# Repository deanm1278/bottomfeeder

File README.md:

# bottomfeeder

demo video of the synthesizer with a control panel added on top is [here](https://youtu.be/Ub5NRgZzTfE).
Note the synthesizer is mounted to the back of the panel in the video.

Features include:
- 3x 16 bit digital Wavetable Oscillators (sample rates up to 200k samples/sec)
  - Fine and coarse tuning controls for each oscillator
  - user loadable waveforms
  - 1 square wave sub oscillator for each oscillator
- Full analog 4 pole resonant low pass filter
- ADSR envelope generator mappable to filter cutoff and VCA
- Monophonic and 3 voice Paraphonic modes
- Glide rate control
- 2x LFO (also any user loadable waveform)
  - Mappable to many parameters including rate or depth of the other LFO
- Headphone output
- External input to filter
- All parameters controllable via Standard MIDI
- Header connections for modification
- Loading and saving presets
- Low cost and small form factor

## Structure
An ARM Cortex M0+ microcontroller acts as a host processor for an [FPGA-Based synthesizer](https://github.com/deanm1278/Chisel-wavetable).
The FPGA outputs the oscillators as well as PWM control voltages for the analog filter and analog VCA parameters.
[Click here](https://github.com/deanm1278/bottomfeeder/blob/master/schematics/synth_revD.pdf) to view PDF schematics.

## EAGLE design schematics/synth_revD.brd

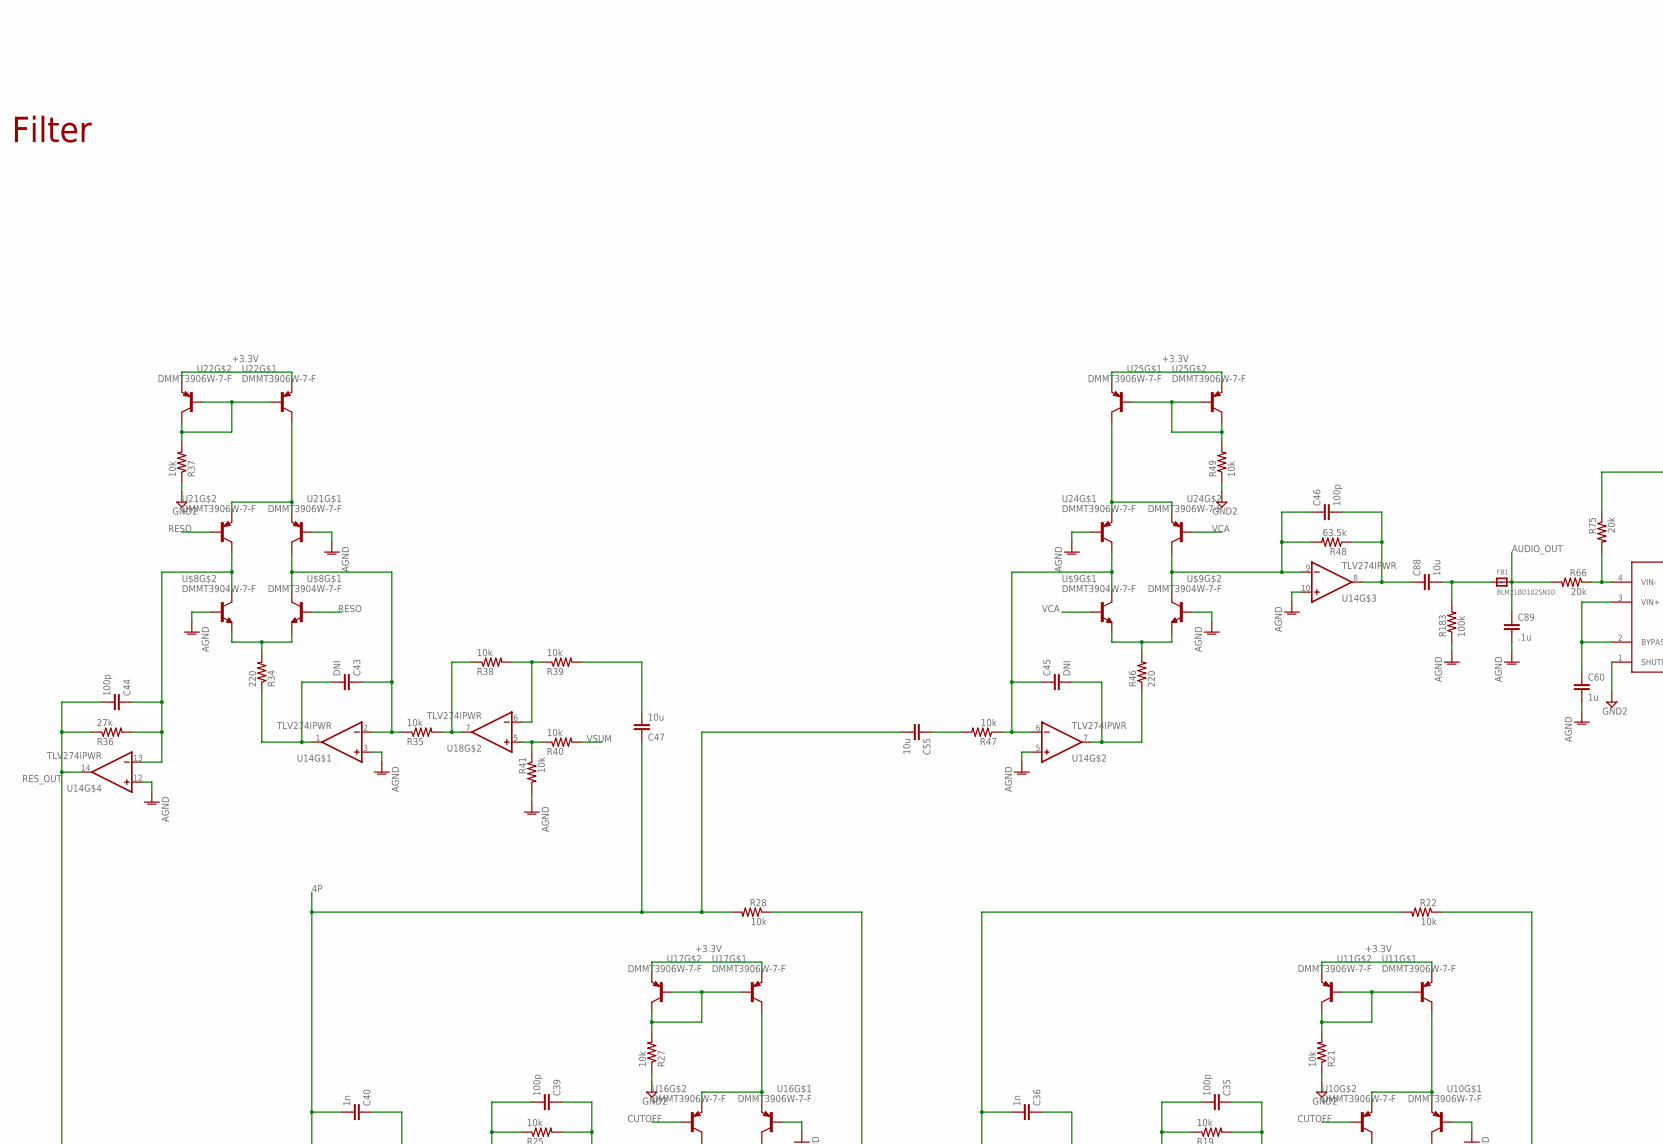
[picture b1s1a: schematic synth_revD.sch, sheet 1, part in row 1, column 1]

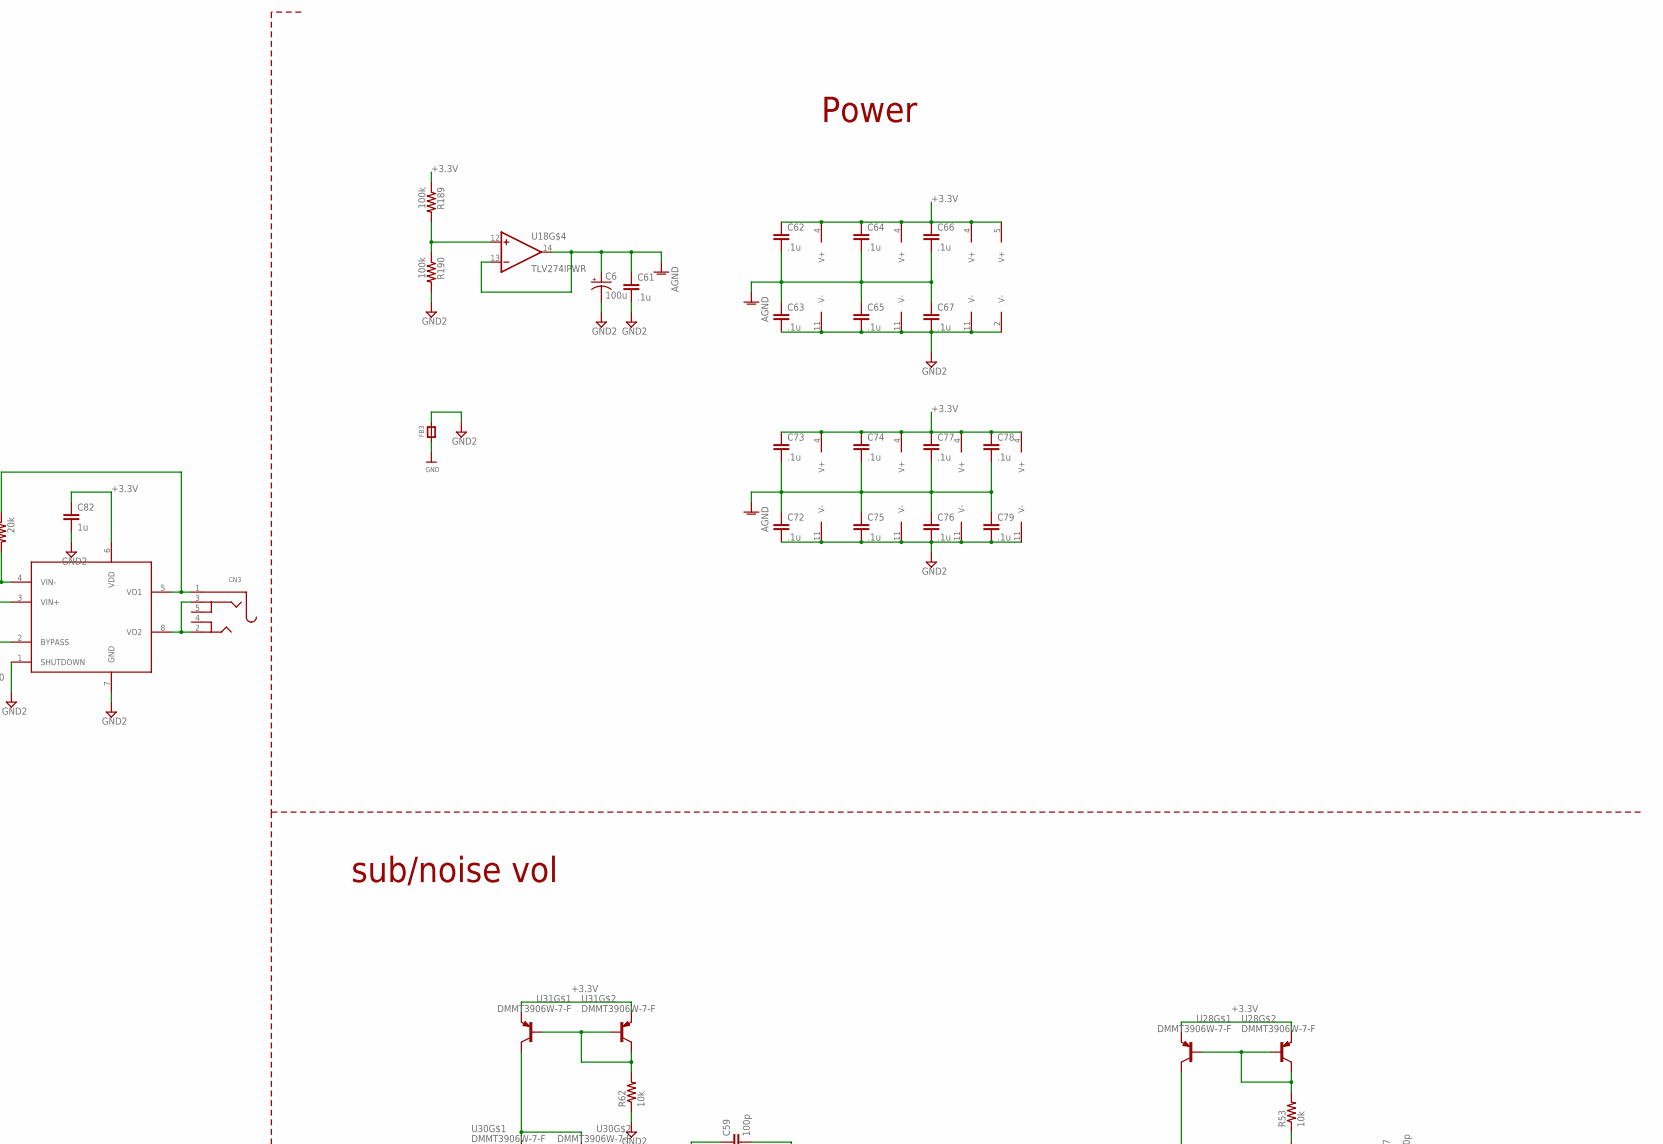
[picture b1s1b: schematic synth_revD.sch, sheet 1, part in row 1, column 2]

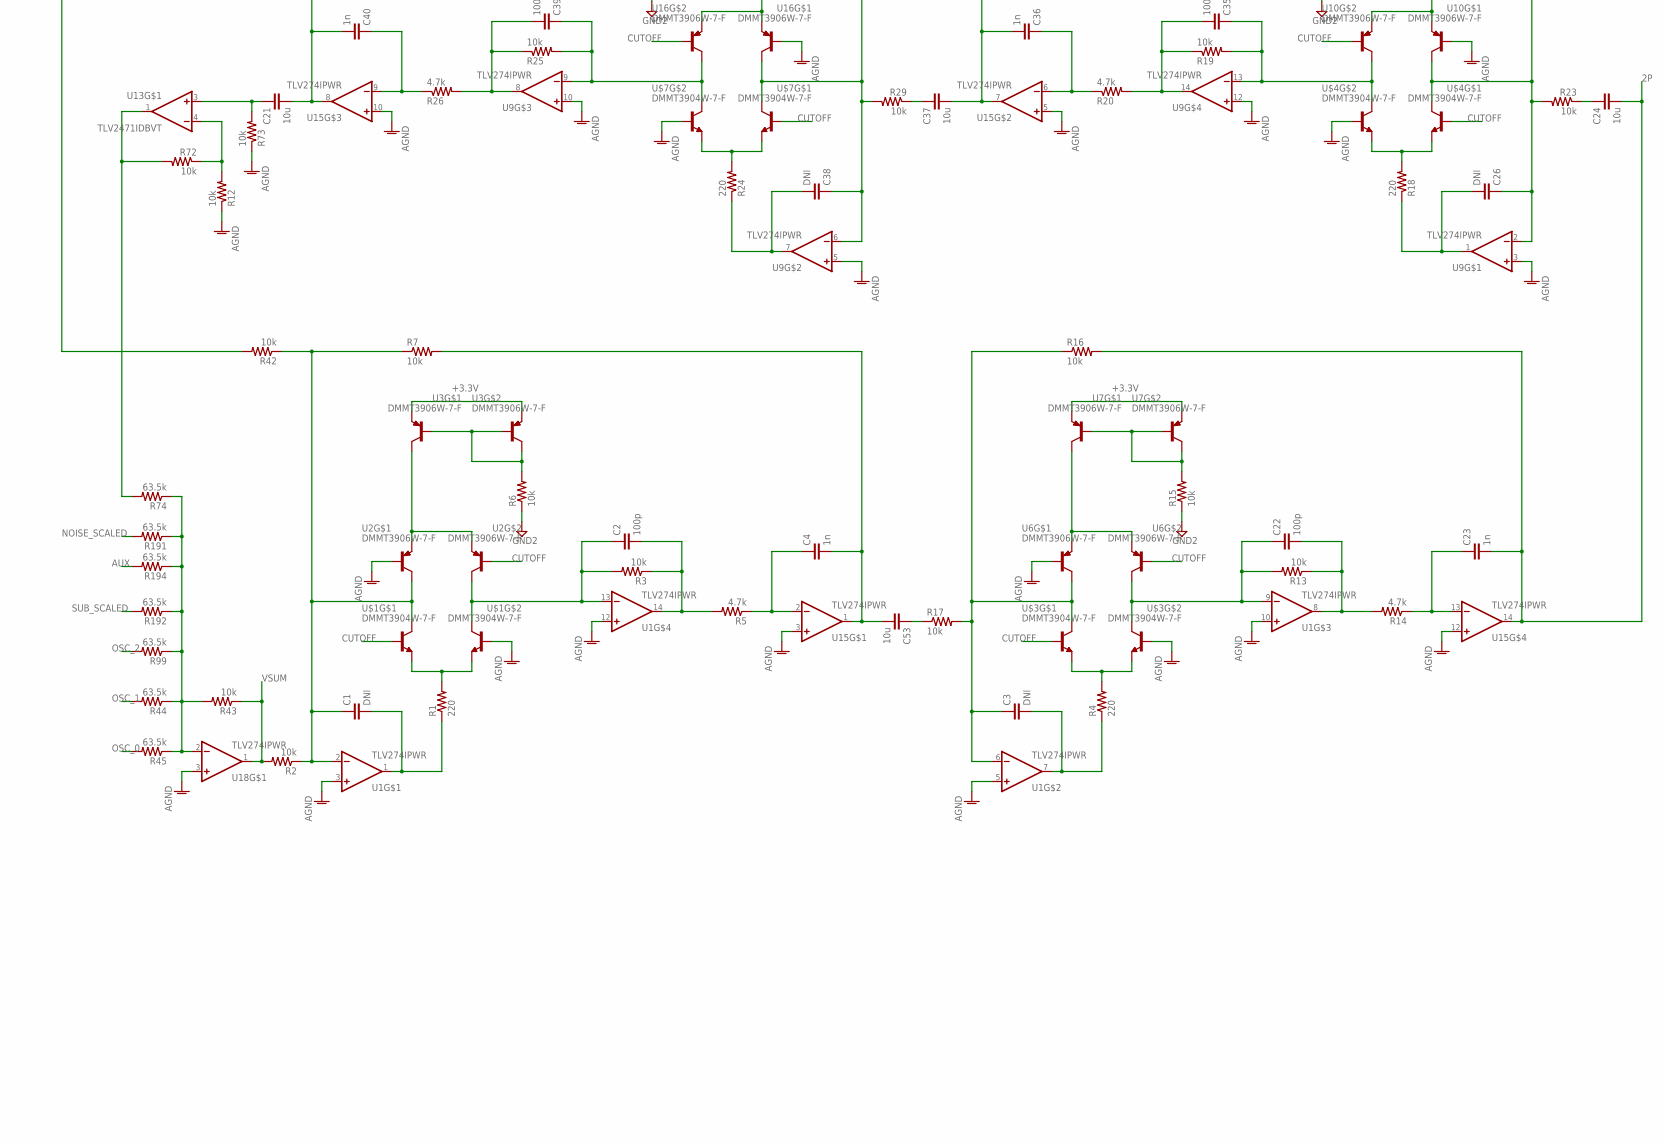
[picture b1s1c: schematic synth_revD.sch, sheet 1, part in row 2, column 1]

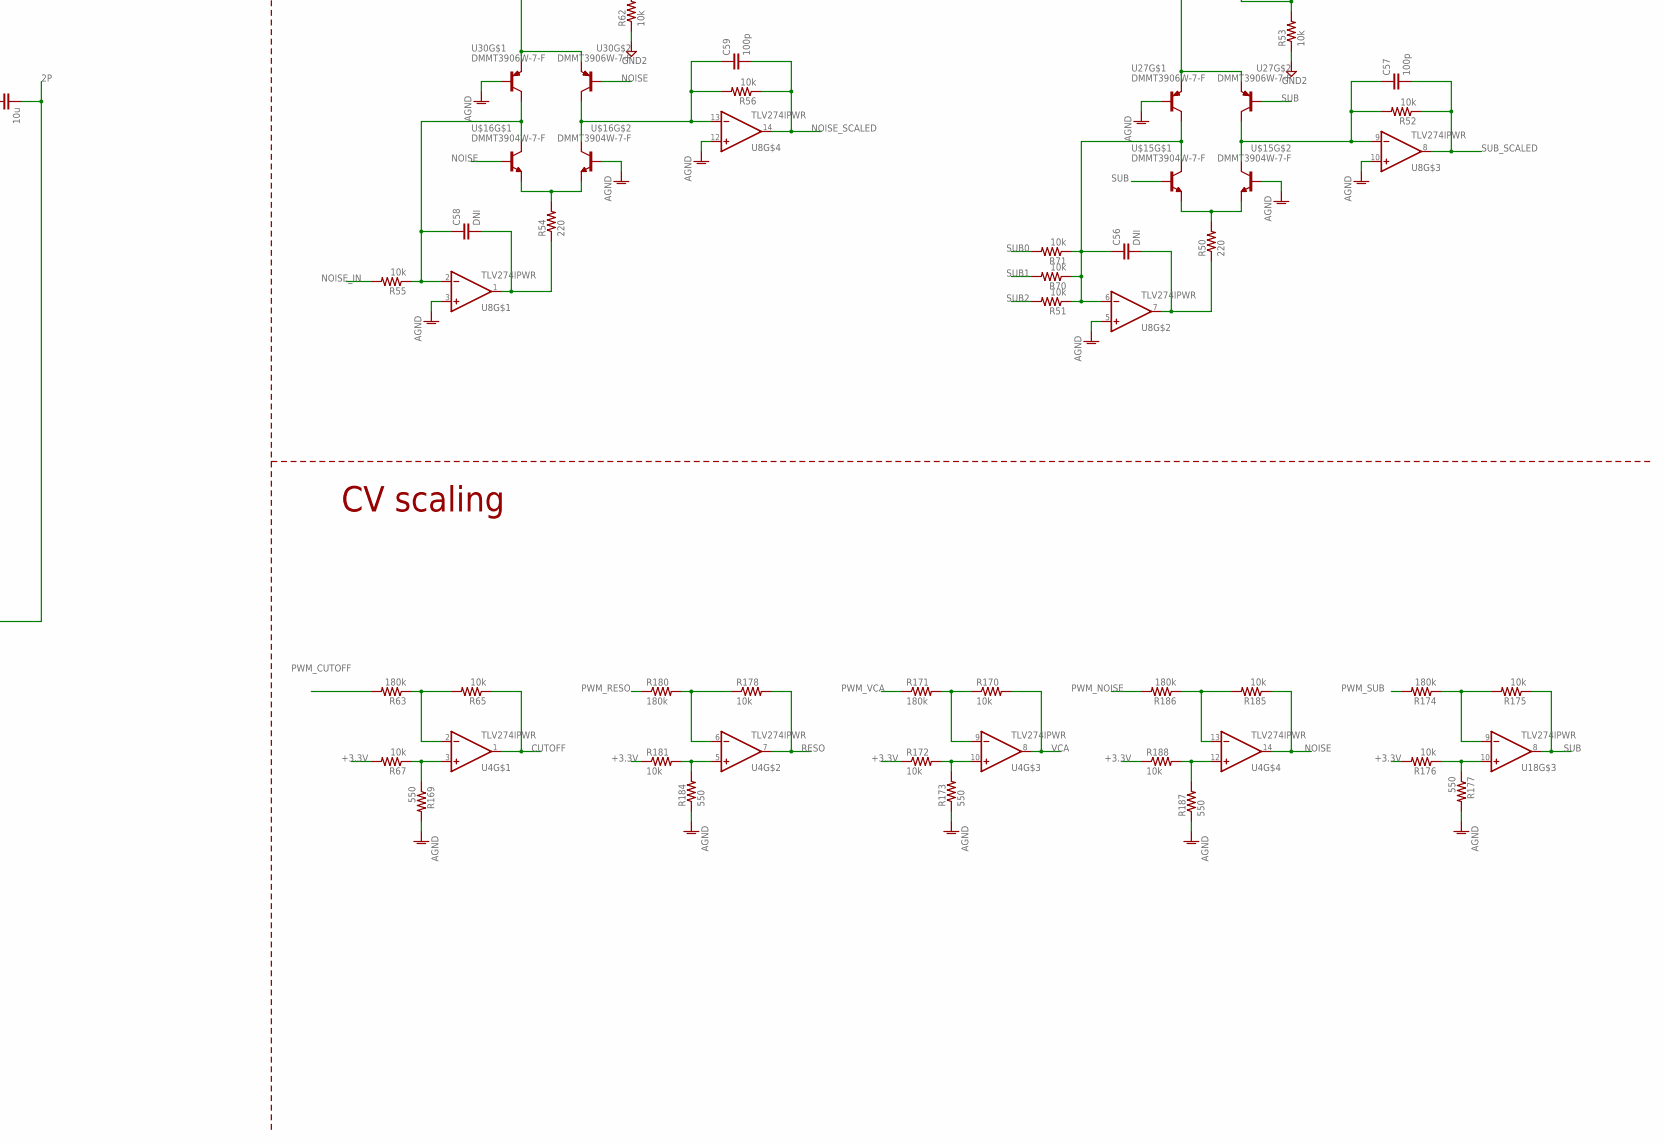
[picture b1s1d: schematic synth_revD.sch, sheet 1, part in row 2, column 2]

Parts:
C1, C3, C26, C38, C43, C45, C56, C58: DNI; C0603
C2, C22, C35, C39, C44, C46, C57, C59: 100p; C0603
C4, C23, C36, C40: 1n; C0603
C6: 100u; PANASONIC_C
C21, C24, C37, C47, C53, C55, C88: 10u; C0603
C60, C82: 1u; C0603
C61, C62, C63, C64, C65, C66, C67, C72, C73, C74, C75, C76, C77, C78, C79, C89: .1u; C0603
CN3: AUDIO_3.5MMJACK; 4UCONN_19269
FB1: BLM21BD102SN1D; 0805
FB3: FERRITE0805; 0805
R1, R4, R18, R24, R34, R46, R50, R54: 220; R0603
R2, R3, R6, R7, R12, R13, R15, R16, R17, R19, R21, R22, R23, R25, R27, R28, R29, R35, R37, R38, R39, R40, R41, R42, R43, R47, R49, R51, R52, R53, R55, R56, R62, R65, R67, R70, R71, R72, R73, R170, R172, R175, R176, R178, R181, R185, R188: 10k; R0603
R5, R14, R20, R26: 4.7k; R0603
R36: 27k; R0603
R44, R45, R48, R74, R99, R191, R192, R194: 63.5k; R0603
R63, R171, R174, R180, R186: 180k; R0603
R66, R75: 20k; R0603
R169, R173, R177, R184, R187: 550; R0603
R183, R189, R190: 100k; R0603
U1, U4, U8, U9, U14, U15, U18: TLV274IPWR; SOP65P640X120-14N
U2, U3, U6, U7, U10, U11, U16, U17, U21, U22, U24, U25, U27, U28, U30, U31: DMMT3906W-7-F; SOT65P210X110-6N
U13: TLV2471IDBVT; SOT95P280X145-5N
U$1, U$3, U$4, U$7, U$8, U$9, U$15, U$16: DMMT3904W-7-F; SOT65P210X100-6N
U$19: LM4819MMX; SOP65P490X110-8N

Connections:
2P: C23.2, C24.2, R16.2, U15.14 (OUT); also elsewhere on the board
4P: C21.2, C40.2, C47.1, C55.2, R28.2, U15.8 (OUT); also elsewhere on the board
$P6543: C46.2, C88.1, R48.1, U14.8 (OUT)
+3.3V: C62.1, C64.1, C66.1, C73.1, C74.1, C77.1, C78.1, C82.1, R67.2, R172.1, R176.2, R181.1, R188.1, R189.1, U1.4 (V+), U3.4 (E), U3.5 (E), U4.4 (V+), U7.4 (E), U7.5 (E), U8.4 (V+), U9.4 (V+), U11.4 (E), U11.5 (E), U13.5 (V+), U14.4 (V+), U15.4 (V+), U17.4 (E), U17.5 (E), U18.4 (V+), U22.4 (E), U22.5 (E), U25.4 (E), U25.5 (E), U28.4 (E), U28.5 (E), U31.4 (E), U31.5 (E), U$19.6 (VDD); also elsewhere on the board
AGND: C6.+, C60.2, C61.1, C62.2, C63.1, C64.2, C65.1, C66.2, C67.1, C72.1, C73.2, C74.2, C75.1, C76.1, C77.2, C78.2, C79.1, C89.2, R12.1, R41.2, R73.1, R169.2, R173.1, R177.2, R183.1, R184.1, R187.1, U1.3 (+IN), U1.5 (+IN), U1.10 (+IN), U1.12 (+IN), U2.2 (B), U6.2 (B), U8.3 (+IN), U8.5 (+IN), U8.10 (+IN), U8.12 (+IN), U9.3 (+IN), U9.5 (+IN), U9.10 (+IN), U9.12 (+IN), U10.2 (B), U14.3 (+IN), U14.5 (+IN), U14.10 (+IN), U14.12 (+IN), U15.3 (+IN), U15.5 (+IN), U15.10 (+IN), U15.12 (+IN), U16.2 (B), U18.3 (+IN), U18.13 (-IN), U18.14 (OUT), U21.2 (B), U24.2 (B), U27.2 (B), U30.2 (B), U$1.1 (B), U$3.1 (B), U$4.1 (B), U$7.1 (B), U$8.1 (B), U$9.1 (B), U$15.1 (B), U$16.1 (B); also elsewhere on the board
AUDIO_OUT: C89.1, FB1.2, R66.2; also elsewhere on the board
AUX: R194.2; also elsewhere on the board
CUTOFF: R65.1, U2.1 (B), U4.1 (OUT), U6.1 (B), U10.1 (B), U16.1 (B), U$1.2 (B), U$3.2 (B), U$4.2 (B), U$7.2 (B)
GND: FB3.1; also elsewhere on the board
GND2: C6.-, C61.2, C63.2, C65.2, C67.2, C72.2, C75.2, C76.2, C79.2, C82.2, FB3.2, R6.1, R15.1, R21.1, R27.1, R37.1, R49.1, R53.1, R62.1, R190.2, U1.11 (V-), U4.11 (V-), U8.11 (V-), U9.11 (V-), U13.2 (V-), U14.11 (V-), U15.11 (V-), U18.11 (V-), U$19.1 (SHUTDOWN), U$19.7 (GND); also elsewhere on the board
unnamed: C1.1, R2.1, R7.1, R42.1, U1.2 (-IN), U2.3 (C), U$1.3 (C)
unnamed: C2.1, R3.2, U1.13 (-IN), U2.6 (C), U$1.6 (C)
unnamed: R1.2, U$1.4 (E), U$1.5 (E)
unnamed: C1.2, R1.1, U1.1 (OUT)
unnamed: R6.2, U3.1 (B), U3.2 (B), U3.6 (C)
unnamed: U2.4 (E), U2.5 (E), U3.3 (C)
unnamed: C2.2, R3.1, R5.2, U1.14 (OUT)
unnamed: C3.1, R16.1, R17.2, U1.6 (-IN), U6.3 (C), U$3.3 (C)
unnamed: C22.1, R13.2, U1.9 (-IN), U6.6 (C), U$3.6 (C)
unnamed: R4.2, U$3.4 (E), U$3.5 (E)
unnamed: C4.1, R5.1, U15.2 (-IN)
unnamed: C3.2, R4.1, U1.7 (OUT)
unnamed: C4.2, C53.2, R7.2, U15.1 (OUT)
unnamed: C21.1, R73.2, U13.3 (+IN)
unnamed: R12.2, R72.1, U13.4 (-IN)
unnamed: R72.2, R74.2, U13.1 (OUT)
unnamed: CN3.2, CN3.3, U$19.8 (VO2)
unnamed: R66.1, R75.2, U$19.4 (VIN-)
unnamed: CN3.1, R75.1, U$19.5 (VO1)
unnamed: R15.2, U7.1 (B), U7.2 (B), U7.6 (C)
unnamed: U6.4 (E), U6.5 (E), U7.3 (C)
unnamed: C22.2, R13.1, R14.2, U1.8 (OUT)
unnamed: C23.1, R14.1, U15.13 (-IN)
unnamed: C53.1, R17.1
unnamed: C26.1, R22.1, R23.2, U9.2 (-IN), U10.3 (C), U$4.3 (C)
unnamed: C35.1, R19.2, U9.13 (-IN), U10.6 (C), U$4.6 (C)
unnamed: R18.2, U$4.4 (E), U$4.5 (E)
unnamed: C26.2, R18.1, U9.1 (OUT)
unnamed: R21.2, U11.1 (B), U11.2 (B), U11.6 (C)
unnamed: U10.4 (E), U10.5 (E), U11.3 (C)
unnamed: C35.2, R19.1, R20.2, U9.14 (OUT)
unnamed: C36.1, R20.1, U15.6 (-IN)
unnamed: C36.2, C37.2, R22.2, U15.7 (OUT)
unnamed: C24.1, R23.1
unnamed: C38.1, R28.1, R29.2, U9.6 (-IN), U16.3 (C), U$7.3 (C)
unnamed: C39.1, R25.2, U9.9 (-IN), U16.6 (C), U$7.6 (C)
unnamed: R24.2, U$7.4 (E), U$7.5 (E)
unnamed: C38.2, R24.1, U9.7 (OUT)
unnamed: R27.2, U17.1 (B), U17.2 (B), U17.6 (C)
unnamed: U16.4 (E), U16.5 (E), U17.3 (C)
unnamed: C39.2, R25.1, R26.2, U9.8 (OUT)
unnamed: C40.1, R26.1, U15.9 (-IN)
unnamed: C37.1, R29.1
unnamed: C60.1, U$19.2 (BYPASS), U$19.3 (VIN+)
unnamed: C56.1, R51.1, R70.1, R71.1, U8.6 (-IN), U27.3 (C), U$15.3 (C)
unnamed: C43.1, R35.1, U14.2 (-IN), U21.3 (C), U$8.3 (C)
unnamed: R67.1, R169.1, U4.3 (+IN)
unnamed: R34.2, U$8.4 (E), U$8.5 (E)
unnamed: C43.2, R34.1, U14.1 (OUT)
unnamed: R37.2, U22.1 (B), U22.2 (B), U22.6 (C)
unnamed: U21.4 (E), U21.5 (E), U22.3 (C)
unnamed: C45.1, R47.1, U14.6 (-IN), U24.3 (C), U$9.3 (C)
unnamed: R40.1, R41.1, U18.5 (+IN)
unnamed: R35.2, R38.1, U18.7 (OUT)
unnamed: R38.2, R39.1, U18.6 (-IN)
unnamed: C46.1, R48.2, U14.9 (-IN), U24.6 (C), U$9.6 (C)
unnamed: C47.2, R39.2
unnamed: R46.2, U$9.4 (E), U$9.5 (E)
unnamed: R43.2, R44.1, R45.1, R74.1, R99.1, R191.1, R192.1, R194.1, U18.2 (-IN)
unnamed: C45.2, R46.1, U14.7 (OUT)
unnamed: C88.2, FB1.1, R183.2
unnamed: R49.2, U25.1 (B), U25.2 (B), U25.6 (C)
unnamed: U24.4 (E), U24.5 (E), U25.3 (C)
unnamed: C55.1, R47.2
unnamed: C57.1, R52.2, U8.9 (-IN), U27.6 (C), U$15.6 (C)
unnamed: R50.2, U$15.4 (E), U$15.5 (E)
unnamed: C56.2, R50.1, U8.7 (OUT)
unnamed: R53.2, U28.1 (B), U28.2 (B), U28.6 (C)
unnamed: U27.4 (E), U27.5 (E), U28.3 (C)
unnamed: C58.1, R55.1, U8.2 (-IN), U30.3 (C), U$16.3 (C)
unnamed: C59.1, R56.2, U8.13 (-IN), U30.6 (C), U$16.6 (C)
unnamed: R54.2, U$16.4 (E), U$16.5 (E)
unnamed: C58.2, R54.1, U8.1 (OUT)
unnamed: R62.2, U31.1 (B), U31.2 (B), U31.6 (C)
unnamed: U30.4 (E), U30.5 (E), U31.3 (C)
unnamed: C44.1, R36.2, U14.13 (-IN), U21.6 (C), U$8.6 (C)
unnamed: R63.1, R65.2, U4.2 (-IN)
unnamed: R176.1, R177.1, U18.10 (+IN)
unnamed: R170.1, R171.2, U4.9 (-IN)
unnamed: R174.1, R175.2, U18.9 (-IN)
unnamed: R172.2, R173.2, U4.10 (+IN)
unnamed: R185.2, R186.1, U4.13 (-IN)
unnamed: R187.2, R188.2, U4.12 (+IN)
unnamed: R181.2, R184.2, U4.5 (+IN)
unnamed: R178.1, R180.2, U4.6 (-IN)
unnamed: R189.2, R190.1, U18.12 (+IN)
NOISE: R185.1, U4.14 (OUT), U30.1 (B), U$16.2 (B)
NOISE_IN: R55.2; also elsewhere on the board
NOISE_SCALED: C59.2, R56.1, R191.2, U8.14 (OUT)
OSC_0: R45.2; also elsewhere on the board
OSC_1: R44.2; also elsewhere on the board
OSC_2: R99.2; also elsewhere on the board
PWM_CUTOFF: R63.2; also elsewhere on the board
PWM_NOISE: R186.2; also elsewhere on the board
PWM_RESO: R180.1; also elsewhere on the board
PWM_SUB: R174.2; also elsewhere on the board
PWM_VCA: R171.1; also elsewhere on the board
RESO: R178.2, U4.7 (OUT), U21.1 (B), U$8.2 (B)
RES_OUT: C44.2, R36.1, R42.2, U14.14 (OUT)
SUB: R175.1, U18.8 (OUT), U27.1 (B), U$15.2 (B)
SUB0: R71.2; also elsewhere on the board
SUB1: R70.2; also elsewhere on the board
SUB2: R51.2; also elsewhere on the board
SUB_SCALED: C57.2, R52.1, R192.2, U8.8 (OUT)
VCA: R170.2, U4.8 (OUT), U24.1 (B), U$9.2 (B)
VSUM: R2.2, R40.2, R43.1, U18.1 (OUT)

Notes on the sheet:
Filter
Power
CV scaling
sub/noise vol

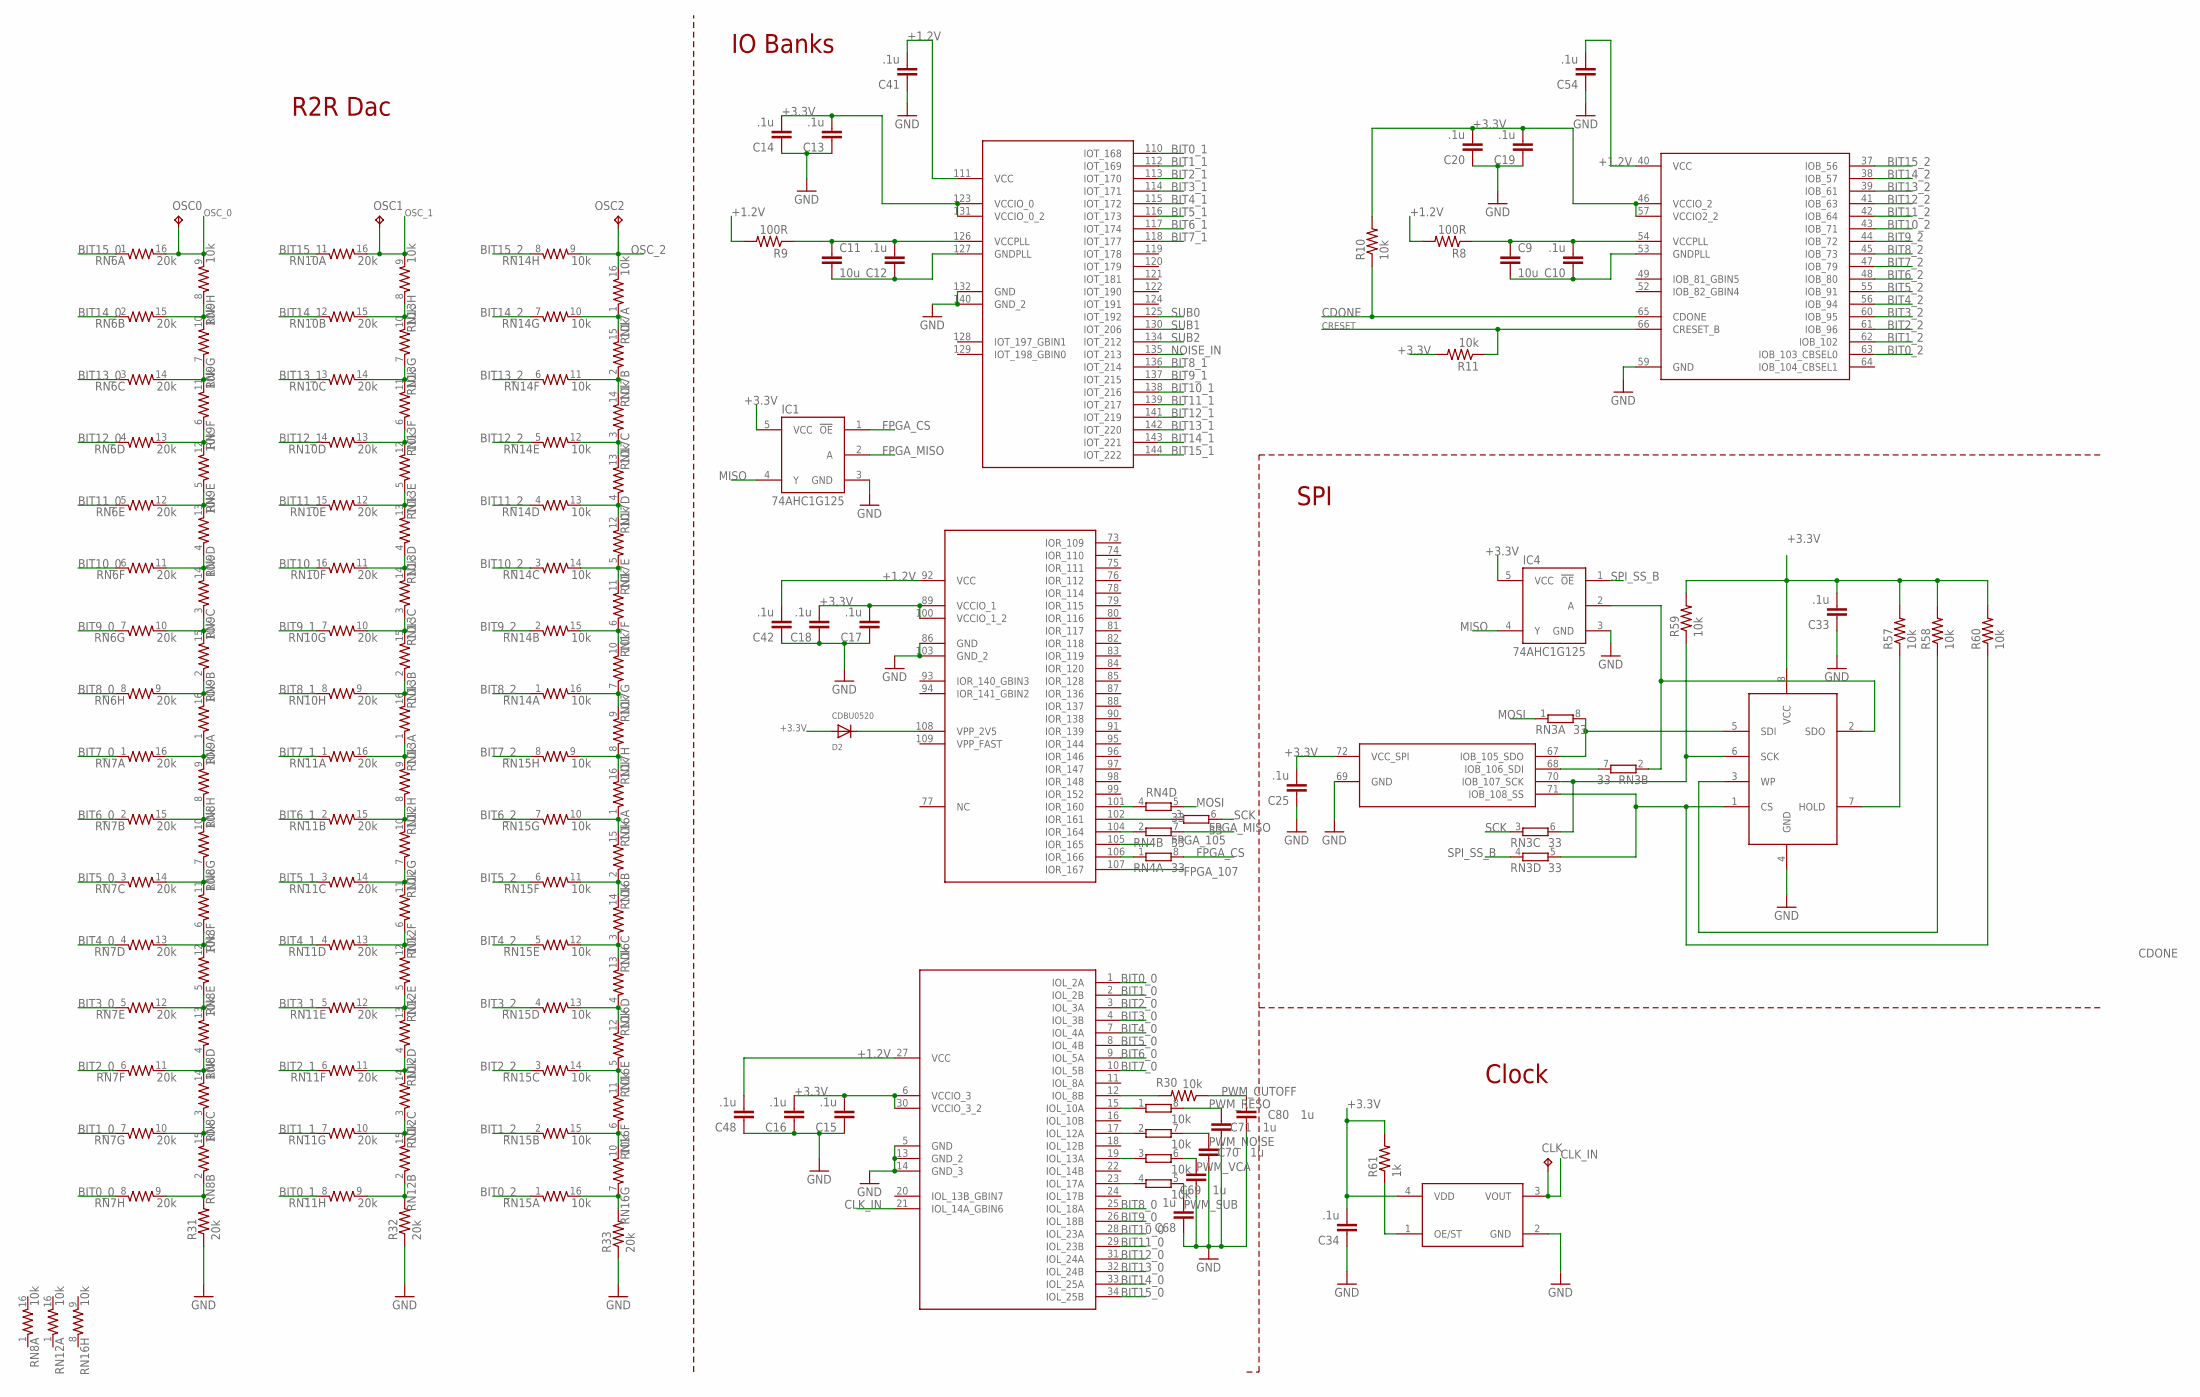
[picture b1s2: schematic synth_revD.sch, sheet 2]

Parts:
C9, C11: 10u; C0603
C10, C12, C13, C14, C15, C16, C17, C18, C19, C20, C25, C33, C34, C41, C42, C48, C54: .1u; C0603
C68, C69, C70, C71, C80: 1u; C0603
CLK: TPB1,27; B1,27
D2: CDBU0520; SOD-523
IC1, IC4: 74AHC1G125; SOT23-5L
OSC0, OSC1, OSC2: TPB1,27; B1,27
R8, R9: 100R; R0603
R10, R11, R30, R57, R58, R59, R60: 10k; R0603
R31, R32, R33: 20k; R0603
R61: 1k; R0603
RAM1: N25Q032A13ESC40FTR; SO08
RN3, RN4: 33; 0603-ARC
RN5: 10k; 0603-ARC
RN6, RN7, RN10, RN11: 20k; 742-16
RN8, RN9, RN12, RN13, RN14, RN15, RN16, RN17: 10k; 742-16
U$2: ICE40HX4K; TQ144
U$5: SIT1602; SMD-43.2X2.5

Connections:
$P534: R59.1, RAM1.6 (SCK), RN3.6 (2), U$2.70 (IOB_107_SCK)
$P789: R60.1, RAM1.1 (CS), RN3.5 (2), U$2.71 (IOB_108_SS)
$P3423: RAM1.5 (SDI), RN3.8 (2), U$2.67 (IOB_105_SDO)
+1.2V: C41.2, C42.2, C48.2, C54.2, R8.2, R9.2, U$2.27 (VCC), U$2.40 (VCC), U$2.92 (VCC), U$2.111 (VCC); also elsewhere on the board
+3.3V: C13.2, C14.2, C15.2, C16.2, C17.2, C18.2, C19.2, C20.2, C25.2, C33.2, C34.2, D2.A, IC1.5 (VCC), IC4.5 (VCC), R10.2, R11.2, R57.2, R58.2, R59.2, R60.2, R61.2, RAM1.8 (VCC), U$2.6 (VCCIO_3), U$2.30 (VCCIO_3_2), U$2.46 (VCCIO_2), U$2.57 (VCCIO2_2), U$2.72 (VCC_SPI), U$2.89 (VCCIO_1), U$2.100 (VCCIO_1_2), U$2.123 (VCCIO_0), U$2.131 (VCCIO_0_2), U$5.4 (VDD); also elsewhere on the board
BIT0_0: RN7.8 (1), U$2.1 (IOL_2A)
BIT0_1: RN11.8 (1), U$2.110 (IOT_168)
BIT0_2: RN15.1, U$2.63 (IOB_103_CBSEL0)
BIT1_0: RN7.7 (1), U$2.2 (IOL_2B)
BIT1_1: RN11.7 (1), U$2.112 (IOT_169)
BIT1_2: RN15.2 (1), U$2.62 (IOB_102)
BIT2_0: RN7.6 (1), U$2.3 (IOL_3A)
BIT2_1: RN11.6 (1), U$2.113 (IOT_170)
BIT2_2: RN15.3 (1), U$2.61 (IOB_96)
BIT3_0: RN7.5 (1), U$2.4 (IOL_3B)
BIT3_1: RN11.5 (1), U$2.114 (IOT_171)
BIT3_2: RN15.4 (1), U$2.60 (IOB_95)
BIT4_0: RN7.4 (1), U$2.7 (IOL_4A)
BIT4_1: RN11.4 (1), U$2.115 (IOT_172)
BIT4_2: RN15.5 (1), U$2.56 (IOB_94)
BIT5_0: RN7.3 (1), U$2.8 (IOL_4B)
BIT5_1: RN11.3 (1), U$2.116 (IOT_173)
BIT5_2: RN15.6 (1), U$2.55 (IOB_91)
BIT6_0: RN7.2 (1), U$2.9 (IOL_5A)
BIT6_1: RN11.2 (1), U$2.117 (IOT_174)
BIT6_2: RN15.7 (1), U$2.48 (IOB_80)
BIT7_0: RN7.1, U$2.10 (IOL_5B)
BIT7_1: RN11.1, U$2.118 (IOT_177)
BIT7_2: RN15.8 (1), U$2.47 (IOB_79)
BIT8_0: RN6.8 (1), U$2.25 (IOL_18A)
BIT8_1: RN10.8 (1), U$2.136 (IOT_214)
BIT8_2: RN14.1, U$2.45 (IOB_73)
BIT9_0: RN6.7 (1), U$2.26 (IOL_18B)
BIT9_1: RN10.7 (1), U$2.137 (IOT_215)
BIT9_2: RN14.2 (1), U$2.44 (IOB_72)
BIT10_0: RN6.6 (1), U$2.28 (IOL_23A)
BIT10_1: RN10.6 (1), U$2.138 (IOT_216)
BIT10_2: RN14.3 (1), U$2.43 (IOB_71)
BIT11_0: RN6.5 (1), U$2.29 (IOL_23B)
BIT11_1: RN10.5 (1), U$2.139 (IOT_217)
BIT11_2: RN14.4 (1), U$2.42 (IOB_64)
BIT12_0: RN6.4 (1), U$2.31 (IOL_24A)
BIT12_1: RN10.4 (1), U$2.141 (IOT_219)
BIT12_2: RN14.5 (1), U$2.41 (IOB_63)
BIT13_0: RN6.3 (1), U$2.32 (IOL_24B)
BIT13_1: RN10.3 (1), U$2.142 (IOT_220)
BIT13_2: RN14.6 (1), U$2.39 (IOB_61)
BIT14_0: RN6.2 (1), U$2.33 (IOL_25A)
BIT14_1: RN10.2 (1), U$2.143 (IOT_221)
BIT14_2: RN14.7 (1), U$2.38 (IOB_57)
BIT15_0: RN6.1, U$2.34 (IOL_25B)
BIT15_1: RN10.1, U$2.144 (IOT_222)
BIT15_2: RN14.8 (1), U$2.37 (IOB_56)
CDONE: R10.1, U$2.65 (CDONE); also elsewhere on the board
CLK_IN: CLK.TP, U$2.21 (IOL_14A_GBIN6), U$5.3 (VOUT)
CRESET: R11.1, U$2.66 (CRESET_B); also elsewhere on the board
FPGA_105: U$2.105 (IOR_165); also elsewhere on the board
FPGA_107: U$2.107 (IOR_167); also elsewhere on the board
FPGA_CS: IC1.1 (!OE), RN4.8 (2); also elsewhere on the board
FPGA_MISO: IC1.2 (A), RN4.7 (2)
GND: C13.1, C14.1, C15.1, C16.1, C17.1, C18.1, C19.1, C20.1, C25.1, C33.1, C34.1, C41.1, C42.1, C48.1, C54.1, C68.1, C69.1, C70.1, C71.1, C80.1, IC1.3 (GND), IC4.3 (GND), R31.1, R32.1, R33.1, RAM1.4 (GND), U$2.5 (GND), U$2.13 (GND_2), U$2.14 (GND_3), U$2.59 (GND), U$2.69 (GND), U$2.86 (GND), U$2.103 (GND_2), U$2.132 (GND), U$2.140 (GND_2), U$5.2 (GND); also elsewhere on the board
MISO: IC1.4 (Y), IC4.4 (Y); also elsewhere on the board
MOSI: RN3.1, RN4.5 (2); also elsewhere on the board
unnamed: R57.1, RAM1.7 (HOLD)
unnamed: R58.1, RAM1.3 (WP)
unnamed: R33.2, RN15.16 (2), RN16.7 (1)
unnamed: R61.1, U$5.1 (OE/ST)
unnamed: RN4.4 (1), U$2.101 (IOR_160)
unnamed: RN14.10 (2), RN17.1, RN17.15 (2)
unnamed: C9.1, C10.2, R8.1, U$2.54 (VCCPLL)
unnamed: C9.2, C10.1, U$2.53 (GNDPLL)
unnamed: C11.1, C12.2, R9.1, U$2.126 (VCCPLL)
unnamed: C11.2, C12.1, U$2.127 (GNDPLL)
unnamed: D2.K (C), U$2.108 (VPP_2V5)
unnamed: R32.2, RN11.9 (2), RN12.2 (1)
unnamed: RN15.15 (2), RN16.6 (1), RN16.10 (2)
unnamed: RN15.14 (2), RN16.5 (1), RN16.11 (2)
unnamed: RN15.13 (2), RN16.4 (1), RN16.12 (2)
unnamed: RN5.4 (1), U$2.23 (IOL_17A)
unnamed: RN3.7 (2), U$2.68 (IOB_106_SDI)
unnamed: RN15.12 (2), RN16.3 (1), RN16.13 (2)
unnamed: RN5.3 (1), U$2.19 (IOL_13A)
unnamed: RN15.11 (2), RN16.2 (1), RN16.14 (2)
unnamed: RN15.10 (2), RN16.1, RN16.15 (2)
unnamed: RN4.3 (1), U$2.102 (IOR_161)
unnamed: RN15.9 (2), RN16.16 (2), RN17.8 (1)
unnamed: RN14.16 (2), RN17.7 (1), RN17.9 (2)
unnamed: RN4.2 (1), U$2.104 (IOR_164)
unnamed: RN4.1, U$2.106 (IOR_166)
unnamed: RN14.15 (2), RN17.6 (1), RN17.10 (2)
unnamed: RN14.14 (2), RN17.5 (1), RN17.11 (2)
unnamed: RN14.13 (2), RN17.4 (1), RN17.12 (2)
unnamed: RN14.12 (2), RN17.3 (1), RN17.13 (2)
unnamed: RN14.11 (2), RN17.2 (1), RN17.14 (2)
unnamed: RN11.10 (2), RN12.3 (1), RN12.15 (2)
unnamed: RN10.15 (2), RN13.8 (1), RN13.10 (2)
unnamed: RN10.14 (2), RN13.7 (1), RN13.11 (2)
unnamed: RN10.13 (2), RN13.6 (1), RN13.12 (2)
unnamed: RN10.12 (2), RN13.5 (1), RN13.13 (2)
unnamed: RN10.11 (2), RN13.4 (1), RN13.14 (2)
unnamed: RN10.10 (2), RN13.3 (1), RN13.15 (2)
unnamed: RN10.9 (2), RN13.2 (1), RN13.16 (2)
unnamed: RN11.16 (2), RN12.9 (2), RN13.1
unnamed: RN11.15 (2), RN12.8 (1), RN12.10 (2)
unnamed: RN11.14 (2), RN12.7 (1), RN12.11 (2)
unnamed: RN11.13 (2), RN12.6 (1), RN12.12 (2)
unnamed: RN11.12 (2), RN12.5 (1), RN12.13 (2)
unnamed: RN11.11 (2), RN12.4 (1), RN12.14 (2)
unnamed: R31.2, RN7.9 (2), RN8.2 (1)
unnamed: RN7.10 (2), RN8.3 (1), RN8.15 (2)
unnamed: RN6.15 (2), RN9.8 (1), RN9.10 (2)
unnamed: RN6.14 (2), RN9.7 (1), RN9.11 (2)
unnamed: RN6.13 (2), RN9.6 (1), RN9.12 (2)
unnamed: RN6.12 (2), RN9.5 (1), RN9.13 (2)
unnamed: RN6.11 (2), RN9.4 (1), RN9.14 (2)
unnamed: RN6.10 (2), RN9.3 (1), RN9.15 (2)
unnamed: RN6.9 (2), RN9.2 (1), RN9.16 (2)
unnamed: RN7.16 (2), RN8.9 (2), RN9.1
unnamed: RN7.15 (2), RN8.8 (1), RN8.10 (2)
unnamed: RN7.14 (2), RN8.7 (1), RN8.11 (2)
unnamed: RN7.13 (2), RN8.6 (1), RN8.12 (2)
unnamed: RN7.12 (2), RN8.5 (1), RN8.13 (2)
unnamed: RN7.11 (2), RN8.4 (1), RN8.14 (2)
unnamed: RN5.2 (1), U$2.17 (IOL_12A)
unnamed: RN5.1, U$2.15 (IOL_10A)
unnamed: R30.2, U$2.12 (IOL_8B)
NOISE_IN: U$2.135 (IOT_213); also elsewhere on the board
OSC_0: OSC0.TP, RN6.16 (2), RN9.9 (2); also elsewhere on the board
OSC_1: OSC1.TP, RN10.16 (2), RN13.9 (2); also elsewhere on the board
OSC_2: OSC2.TP, RN14.9 (2), RN17.16 (2); also elsewhere on the board
PWM_CUTOFF: C80.2, R30.1; also elsewhere on the board
PWM_NOISE: C70.2, RN5.7 (2); also elsewhere on the board
PWM_RESO: C71.2, RN5.8 (2); also elsewhere on the board
PWM_SUB: C68.2, RN5.5 (2); also elsewhere on the board
PWM_VCA: C69.2, RN5.6 (2); also elsewhere on the board
SCK: RN3.3 (1), RN4.6 (2); also elsewhere on the board
SPI_SDI: IC4.2 (A), RAM1.2 (SDO), RN3.2 (1)
SPI_SS_B: IC4.1 (!OE), RN3.4 (1); also elsewhere on the board
SUB0: U$2.125 (IOT_192); also elsewhere on the board
SUB1: U$2.130 (IOT_206); also elsewhere on the board
SUB2: U$2.134 (IOT_212); also elsewhere on the board

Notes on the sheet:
R2R Dac
IO Banks
SPI
Clock

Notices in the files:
ArduinoCore/src/variants/variant.cpp:
Copyright (c) 2014-2015 Arduino LLC.  All right reserved.
parts and their libraries:
microbuilder: This work is placed in the public domain, and may be freely used for commercial and non-commercial work with the following conditions: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
resistor-array: Copyright (C) 2008, Bob Starr
